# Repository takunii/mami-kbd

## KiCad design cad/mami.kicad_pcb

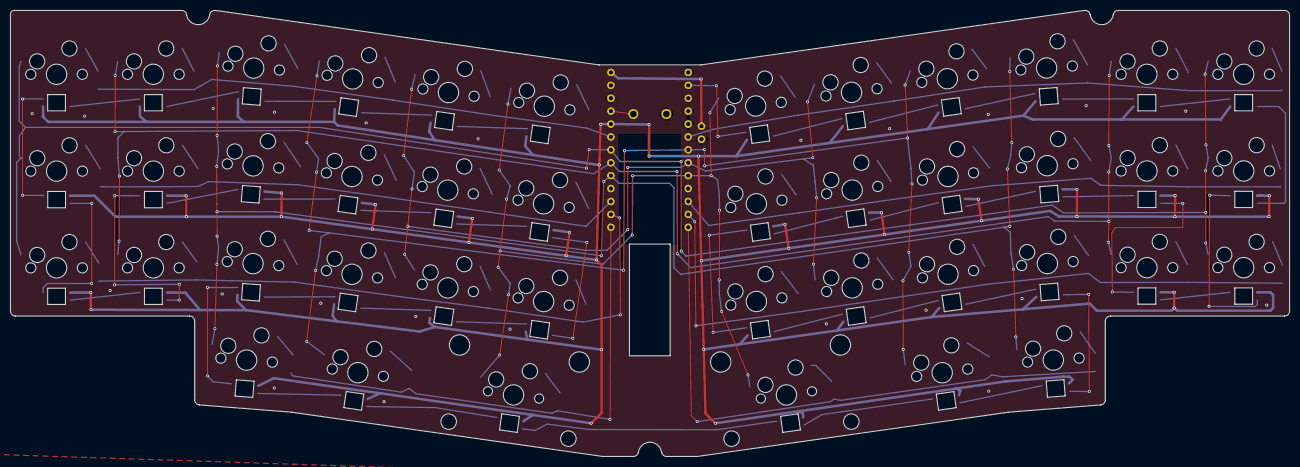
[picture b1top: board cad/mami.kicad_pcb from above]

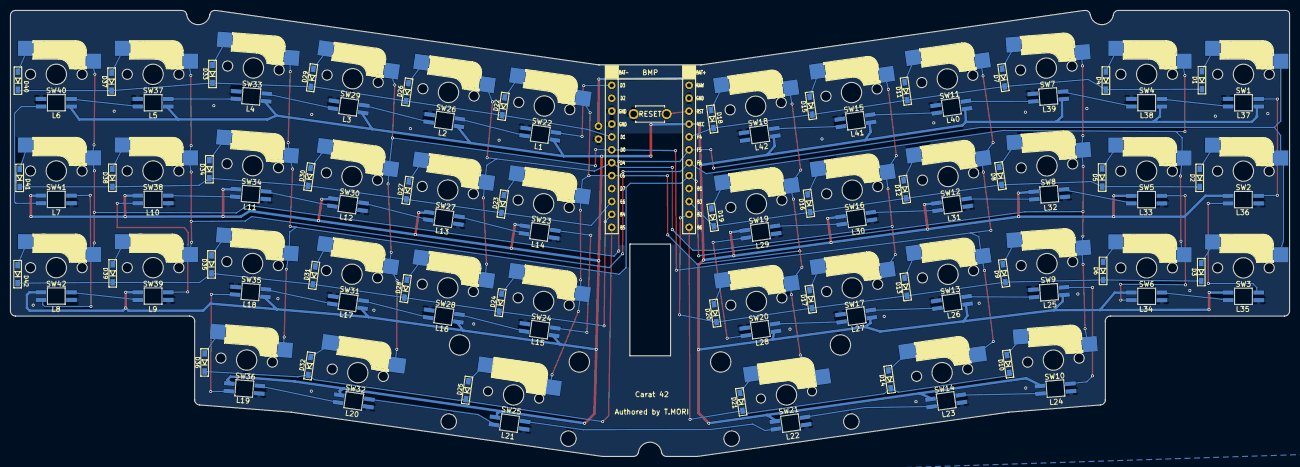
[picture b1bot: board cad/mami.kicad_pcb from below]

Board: 2 copper layers, 251.8 x 87.8 mm, 129 parts (2 on the bottom side), 102 nets.

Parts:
D1, D2, D3, D4, D5, D6, D7, D8, D9, D10, D11, D12, D13, D14, D15, D16, D17, D18, D19, D20, D21, D22, D23, D24, D25, D26, D27, D28, D29, D30, D31, D32, D33, D34, D35, D36, D37, D38, D39, D40, D41, D42: 1N4148W; Diode_SMD
J1: Conn_01x02_Pin; Battery_BMP_2pin
L1, L2, L3, L4, L5, L6, L7, L8, L9, L10, L11, L12, L13, L14, L15, L16, L17, L18, L19, L20, L21, L22, L23, L24, L25, L26, L27, L28, L29, L30, L31, L32, L33, L34, L35, L36, L37, L38, L39, L40, L41, L42: SK6812MINI-E; LED_SK6812MINI-E_BL
SW1, SW2, SW3, SW4, SW5, SW6, SW7, SW8, SW9, SW10, SW11, SW12, SW13, SW15, SW16, SW17, SW18, SW19, SW20, SW22, SW23, SW24, SW26, SW27, SW28, SW29, SW30, SW31, SW33, SW34, SW35, SW36, SW37, SW38, SW39, SW40, SW41, SW42: SW_Push; CherryMX_Hotswap_1u
SW14, SW32: SW_Push; CherryMX_Hotswap_1.25u
SW21, SW25: SW_Push; CherryMX_Hotswap_2u
SW43: ResetSW
U1: Micon_BLEMicroPro; Micon_BMP_7sKB

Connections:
BAT+: J1.2, U1.25 (BAT+)
GND: J1.1, L1.1 (VSS), L2.1 (VSS), L3.1 (VSS), L4.1 (VSS), L5.1 (VSS), L6.1 (VSS), L7.1 (VSS), L8.1 (VSS), L9.1 (VSS), L10.1 (VSS), L11.1 (VSS), L12.1 (VSS), L13.1 (VSS), L14.1 (VSS), L15.1 (VSS), L16.1 (VSS), L17.1 (VSS), L18.1 (VSS), L19.1 (VSS), L20.1 (VSS), L21.1 (VSS), L22.1 (VSS), L23.1 (VSS), L24.1 (VSS), L25.1 (VSS), L26.1 (VSS), L27.1 (VSS), L28.1 (VSS), L29.1 (VSS), L30.1 (VSS), L31.1 (VSS), L32.1 (VSS), L33.1 (VSS), L34.1 (VSS), L35.1 (VSS), L36.1 (VSS), L37.1 (VSS), L38.1 (VSS), L39.1 (VSS), L40.1 (VSS), L41.1 (VSS), L42.1 (VSS), SW43.1, U1.3 (GND), U1.4 (GND), U1.23 (GND), U1.26 (BAT-)
LED: L1.2 (DIN), U1.1 (D3/PIN1)
unnamed: D1.2 (A), SW1.2
unnamed: D2.2 (A), SW2.2
unnamed: D3.2 (A), SW3.2
unnamed: D4.2 (A), SW4.2
unnamed: D5.2 (A), SW5.2
unnamed: D6.2 (A), SW6.2
unnamed: D7.2 (A), SW7.2
unnamed: D8.2 (A), SW8.2
unnamed: D9.2 (A), SW9.2
unnamed: D10.2 (A), SW10.2
unnamed: D11.2 (A), SW11.2
unnamed: D12.2 (A), SW12.2
unnamed: D13.2 (A), SW13.2
unnamed: D14.2 (A), SW14.2
unnamed: D15.2 (A), SW15.2
unnamed: D16.2 (A), SW16.2
unnamed: D17.2 (A), SW17.2
unnamed: D18.2 (A), SW18.2
unnamed: D19.2 (A), SW19.2
unnamed: D20.2 (A), SW20.2
unnamed: D21.2 (A), SW21.2
unnamed: D22.2 (A), SW22.2
unnamed: D23.2 (A), SW23.2
unnamed: D24.2 (A), SW24.2
unnamed: D25.2 (A), SW25.2
unnamed: D26.2 (A), SW26.2
unnamed: D27.2 (A), SW27.2
unnamed: D28.2 (A), SW28.2
unnamed: D29.2 (A), SW29.2
unnamed: D30.2 (A), SW30.2
unnamed: D31.2 (A), SW31.2
unnamed: D32.2 (A), SW32.2
unnamed: D33.2 (A), SW33.2
unnamed: D34.2 (A), SW34.2
unnamed: D35.2 (A), SW35.2
unnamed: D36.2 (A), SW36.2
unnamed: D37.2 (A), SW37.2
unnamed: D38.2 (A), SW38.2
unnamed: D39.2 (A), SW39.2
unnamed: D40.2 (A), SW40.2
unnamed: D41.2 (A), SW41.2
unnamed: D42.2 (A), SW42.2
unnamed: L1.4 (DOUT), L2.2 (DIN)
unnamed: L2.4 (DOUT), L3.2 (DIN)
unnamed: L3.4 (DOUT), L4.2 (DIN)
unnamed: L4.4 (DOUT), L5.2 (DIN)
unnamed: L5.4 (DOUT), L6.2 (DIN)
unnamed: L6.4 (DOUT), L7.2 (DIN)
unnamed: L7.4 (DOUT), L8.2 (DIN)
unnamed: L8.4 (DOUT), L9.2 (DIN)
unnamed: L9.4 (DOUT), L10.2 (DIN)
unnamed: L10.4 (DOUT), L11.2 (DIN)
unnamed: L11.4 (DOUT), L12.2 (DIN)
unnamed: L12.4 (DOUT), L13.2 (DIN)
unnamed: L13.4 (DOUT), L14.2 (DIN)
unnamed: L14.4 (DOUT), L15.2 (DIN)
unnamed: L15.4 (DOUT), L16.2 (DIN)
unnamed: L16.4 (DOUT), L17.2 (DIN)
unnamed: L17.4 (DOUT), L18.2 (DIN)
unnamed: L18.4 (DOUT), L19.2 (DIN)
unnamed: L19.4 (DOUT), L20.2 (DIN)
unnamed: L20.4 (DOUT), L21.2 (DIN)
unnamed: L21.4 (DOUT), L22.2 (DIN)
unnamed: L22.4 (DOUT), L23.2 (DIN)
unnamed: L23.4 (DOUT), L24.2 (DIN)
unnamed: L24.4 (DOUT), L25.2 (DIN)
unnamed: L25.4 (DOUT), L26.2 (DIN)
unnamed: L26.4 (DOUT), L27.2 (DIN)
unnamed: L27.4 (DOUT), L28.2 (DIN)
unnamed: L28.4 (DOUT), L29.2 (DIN)
unnamed: L29.4 (DOUT), L30.2 (DIN)
unnamed: L30.4 (DOUT), L31.2 (DIN)
unnamed: L31.4 (DOUT), L32.2 (DIN)
unnamed: L32.4 (DOUT), L33.2 (DIN)
unnamed: L33.4 (DOUT), L34.2 (DIN)
unnamed: L34.4 (DOUT), L35.2 (DIN)
unnamed: L35.4 (DOUT), L36.2 (DIN)
unnamed: L36.4 (DOUT), L37.2 (DIN)
unnamed: L37.4 (DOUT), L38.2 (DIN)
unnamed: L38.4 (DOUT), L39.2 (DIN)
unnamed: L39.4 (DOUT), L40.2 (DIN)
unnamed: L40.4 (DOUT), L41.2 (DIN)
unnamed: L41.4 (DOUT), L42.2 (DIN)
VCC: L1.3 (VDD), L2.3 (VDD), L3.3 (VDD), L4.3 (VDD), L5.3 (VDD), L6.3 (VDD), L7.3 (VDD), L8.3 (VDD), L9.3 (VDD), L10.3 (VDD), L11.3 (VDD), L12.3 (VDD), L13.3 (VDD), L14.3 (VDD), L15.3 (VDD), L16.3 (VDD), L17.3 (VDD), L18.3 (VDD), L19.3 (VDD), L20.3 (VDD), L21.3 (VDD), L22.3 (VDD), L23.3 (VDD), L24.3 (VDD), L25.3 (VDD), L26.3 (VDD), L27.3 (VDD), L28.3 (VDD), L29.3 (VDD), L30.3 (VDD), L31.3 (VDD), L32.3 (VDD), L33.3 (VDD), L34.3 (VDD), L35.3 (VDD), L36.3 (VDD), L37.3 (VDD), L38.3 (VDD), L39.3 (VDD), L40.3 (VDD), L41.3 (VDD), L42.3 (VDD), U1.21 (VCC)
col0: SW1.1, SW2.1, SW3.1, SW40.1, SW41.1, SW42.1, U1.19 (F5/PIN19)
col1: SW4.1, SW5.1, SW6.1, SW37.1, SW38.1, SW39.1, U1.18 (F6/PIN18)
col2: SW7.1, SW8.1, SW9.1, SW10.1, SW33.1, SW34.1, SW35.1, SW36.1, U1.17 (F7/PIN17)
col3: SW11.1, SW12.1, SW13.1, SW14.1, SW29.1, SW30.1, SW31.1, SW32.1, U1.6 (D0/PIN6/SCL)
col4: SW15.1, SW16.1, SW17.1, SW26.1, SW27.1, SW28.1, U1.7 (D4/PIN7)
col5: SW18.1, SW19.1, SW20.1, SW21.1, SW22.1, SW23.1, SW24.1, SW25.1, U1.8 (C6/PIN8)
reset: SW43.2, U1.22 (RST)
row0: D1.1 (K), D4.1 (K), D7.1 (K), D11.1 (K), D15.1 (K), D18.1 (K), U1.20 (F4/PIN20)
row1: D2.1 (K), D5.1 (K), D8.1 (K), D12.1 (K), D16.1 (K), D19.1 (K), U1.15 (B3/PIN15)
row2: D3.1 (K), D6.1 (K), D9.1 (K), D13.1 (K), D17.1 (K), D20.1 (K), U1.14 (B2/PIN14)
row3: D10.1 (K), D14.1 (K), D21.1 (K), U1.13 (B6/PIN13)
row4: D22.1 (K), D26.1 (K), D29.1 (K), D33.1 (K), D37.1 (K), D40.1 (K), U1.5 (D1/PIN5/SDA)
row5: D23.1 (K), D27.1 (K), D30.1 (K), D34.1 (K), D38.1 (K), D41.1 (K), U1.10 (E6/PIN10)
row6: D24.1 (K), D28.1 (K), D31.1 (K), D35.1 (K), D39.1 (K), D42.1 (K), U1.11 (B4/PIN11)
row7: D25.1 (K), D32.1 (K), D36.1 (K), U1.12 (B5/PIN12)

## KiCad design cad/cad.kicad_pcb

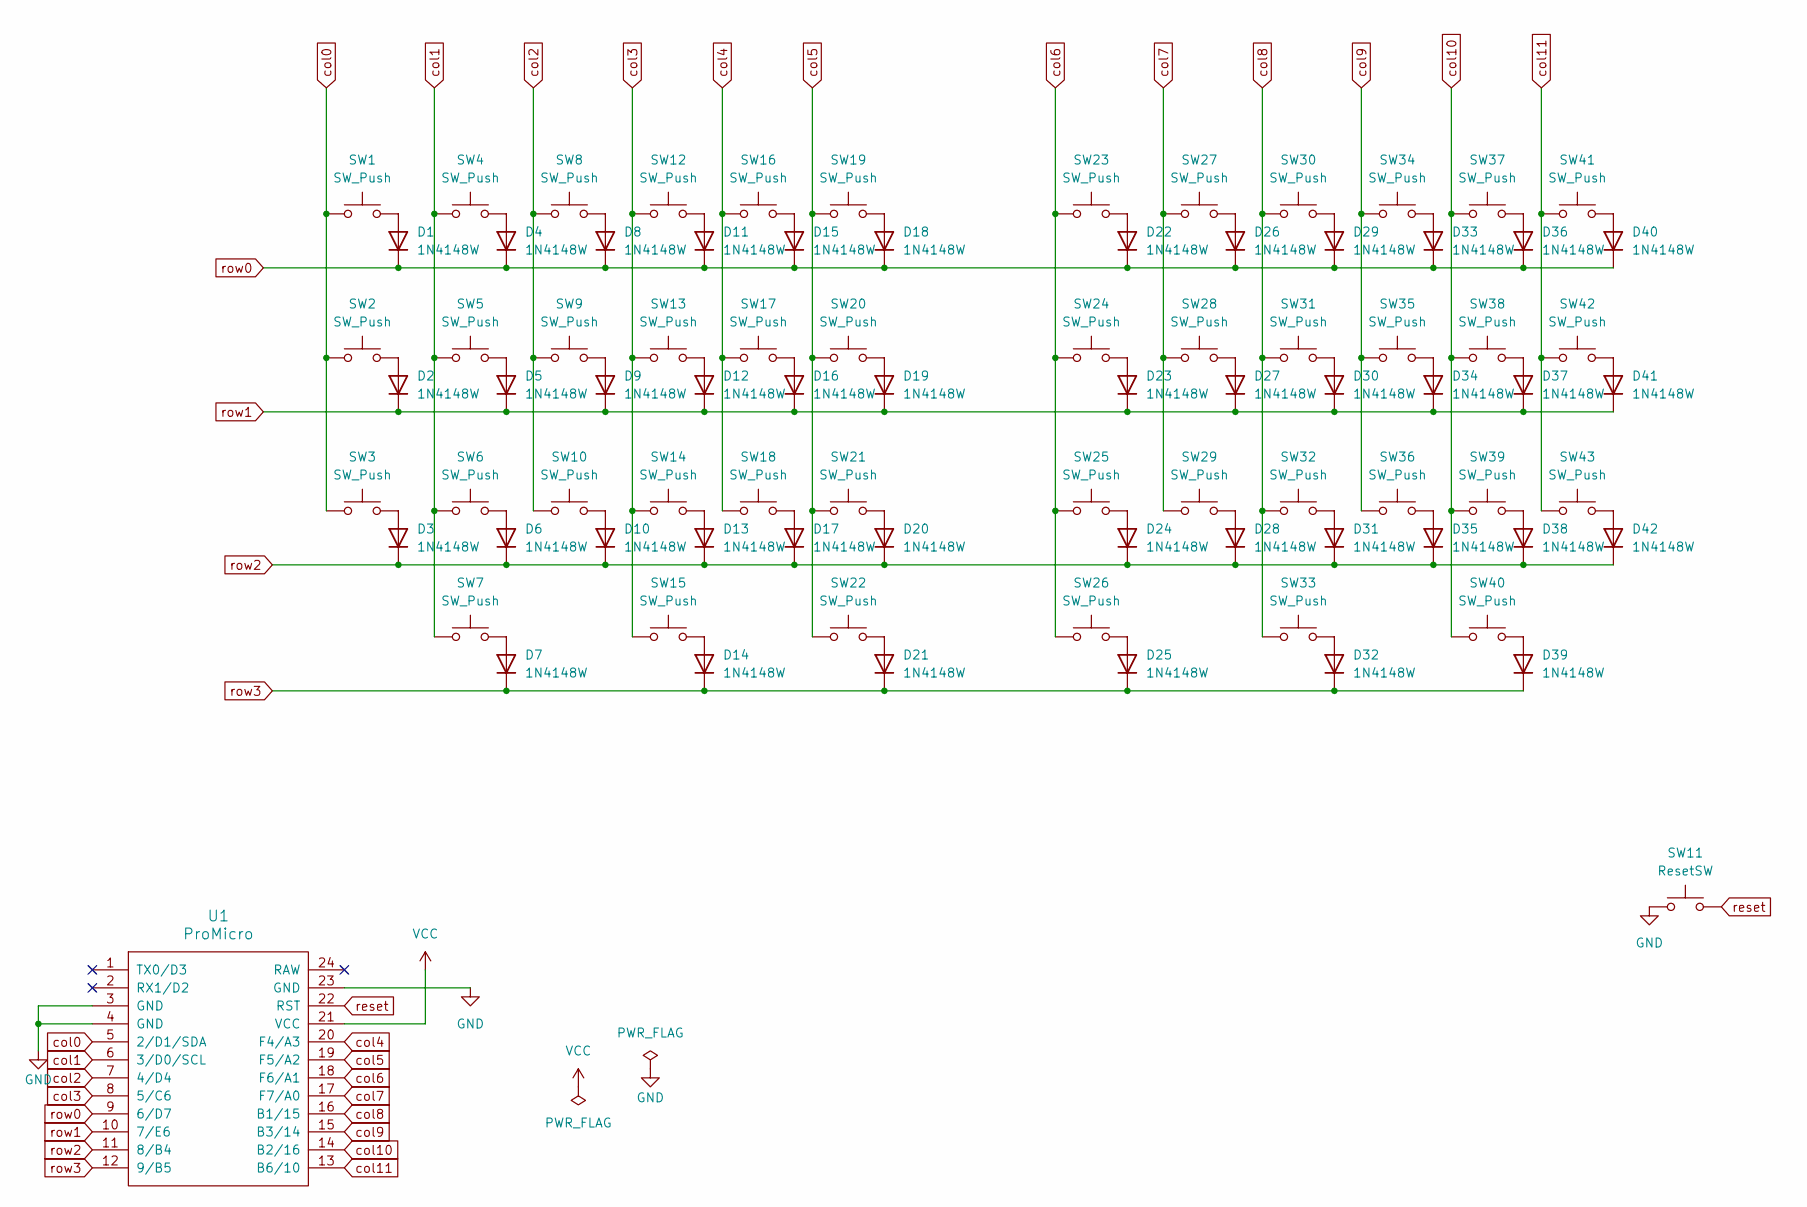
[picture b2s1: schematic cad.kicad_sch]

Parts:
D1, D2, D3, D4, D5, D6, D7, D8, D9, D10, D11, D12, D13, D14, D15, D16, D17, D18, D19, D20, D21, D22, D23, D24, D25, D26, D27, D28, D29, D30, D31, D32, D33, D34, D35, D36, D37, D38, D39, D40, D41, D42: 1N4148W; D_SOD-123
SW1, SW2, SW3, SW4, SW5, SW6, SW7, SW8, SW9, SW10, SW12, SW13, SW14, SW15, SW16, SW17, SW18, SW19, SW20, SW21, SW22, SW23, SW24, SW25, SW26, SW27, SW28, SW29, SW30, SW31, SW32, SW33, SW34, SW35, SW36, SW37, SW38, SW39, SW40, SW41, SW42, SW43: SW_Push; keyswitch_cherrymx_hotswap_1u
SW11: ResetSW
U1: ProMicro

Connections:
GND: SW11.1, U1.3 (GND), U1.4 (GND), U1.23 (GND)
unnamed: D1.2 (A), SW1.2
unnamed: D2.2 (A), SW2.2
unnamed: D3.2 (A), SW3.2
unnamed: D4.2 (A), SW4.2
unnamed: D5.2 (A), SW5.2
unnamed: D6.2 (A), SW6.2
unnamed: D7.2 (A), SW7.2
unnamed: D8.2 (A), SW8.2
unnamed: D9.2 (A), SW9.2
unnamed: D10.2 (A), SW10.2
unnamed: D11.2 (A), SW12.2
unnamed: D12.2 (A), SW13.2
unnamed: D13.2 (A), SW14.2
unnamed: D14.2 (A), SW15.2
unnamed: D15.2 (A), SW16.2
unnamed: D16.2 (A), SW17.2
unnamed: D17.2 (A), SW18.2
unnamed: D18.2 (A), SW19.2
unnamed: D19.2 (A), SW20.2
unnamed: D20.2 (A), SW21.2
unnamed: D21.2 (A), SW22.2
unnamed: D22.2 (A), SW23.2
unnamed: D23.2 (A), SW24.2
unnamed: D24.2 (A), SW25.2
unnamed: D25.2 (A), SW26.2
unnamed: D26.2 (A), SW27.2
unnamed: D27.2 (A), SW28.2
unnamed: D28.2 (A), SW29.2
unnamed: D29.2 (A), SW30.2
unnamed: D30.2 (A), SW31.2
unnamed: D31.2 (A), SW32.2
unnamed: D32.2 (A), SW33.2
unnamed: D33.2 (A), SW34.2
unnamed: D34.2 (A), SW35.2
unnamed: D35.2 (A), SW36.2
unnamed: D36.2 (A), SW37.2
unnamed: D37.2 (A), SW38.2
unnamed: D38.2 (A), SW39.2
unnamed: D39.2 (A), SW40.2
unnamed: D40.2 (A), SW41.2
unnamed: D41.2 (A), SW42.2
unnamed: D42.2 (A), SW43.2
VCC: U1.21 (VCC)
col0: SW1.1, SW2.1, SW3.1, U1.5 (2/D1/SDA)
col1: SW4.1, SW5.1, SW6.1, SW7.1, U1.6 (3/D0/SCL)
col2: SW8.1, SW9.1, SW10.1, U1.7 (4/D4)
col3: SW12.1, SW13.1, SW14.1, SW15.1, U1.8 (5/C6)
col4: SW16.1, SW17.1, SW18.1, U1.20 (F4/A3)
col5: SW19.1, SW20.1, SW21.1, SW22.1, U1.19 (F5/A2)
col6: SW23.1, SW24.1, SW25.1, SW26.1, U1.18 (F6/A1)
col7: SW27.1, SW28.1, SW29.1, U1.17 (F7/A0)
col8: SW30.1, SW31.1, SW32.1, SW33.1, U1.16 (B1/15)
col9: SW34.1, SW35.1, SW36.1, U1.15 (B3/14)
col10: SW37.1, SW38.1, SW39.1, SW40.1, U1.14 (B2/16)
col11: SW41.1, SW42.1, SW43.1, U1.13 (B6/10)
reset: SW11.2, U1.22 (RST)
row0: D1.1 (K), D4.1 (K), D8.1 (K), D11.1 (K), D15.1 (K), D18.1 (K), D22.1 (K), D26.1 (K), D29.1 (K), D33.1 (K), D36.1 (K), D40.1 (K), U1.9 (6/D7)
row1: D2.1 (K), D5.1 (K), D9.1 (K), D12.1 (K), D16.1 (K), D19.1 (K), D23.1 (K), D27.1 (K), D30.1 (K), D34.1 (K), D37.1 (K), D41.1 (K), U1.10 (7/E6)
row2: D3.1 (K), D6.1 (K), D10.1 (K), D13.1 (K), D17.1 (K), D20.1 (K), D24.1 (K), D28.1 (K), D31.1 (K), D35.1 (K), D38.1 (K), D42.1 (K), U1.11 (8/B4)
row3: D7.1 (K), D14.1 (K), D21.1 (K), D25.1 (K), D32.1 (K), D39.1 (K), U1.12 (9/B5)

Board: 2 copper layers, 86 parts (0 on the bottom side), 60 nets, no tracks yet.

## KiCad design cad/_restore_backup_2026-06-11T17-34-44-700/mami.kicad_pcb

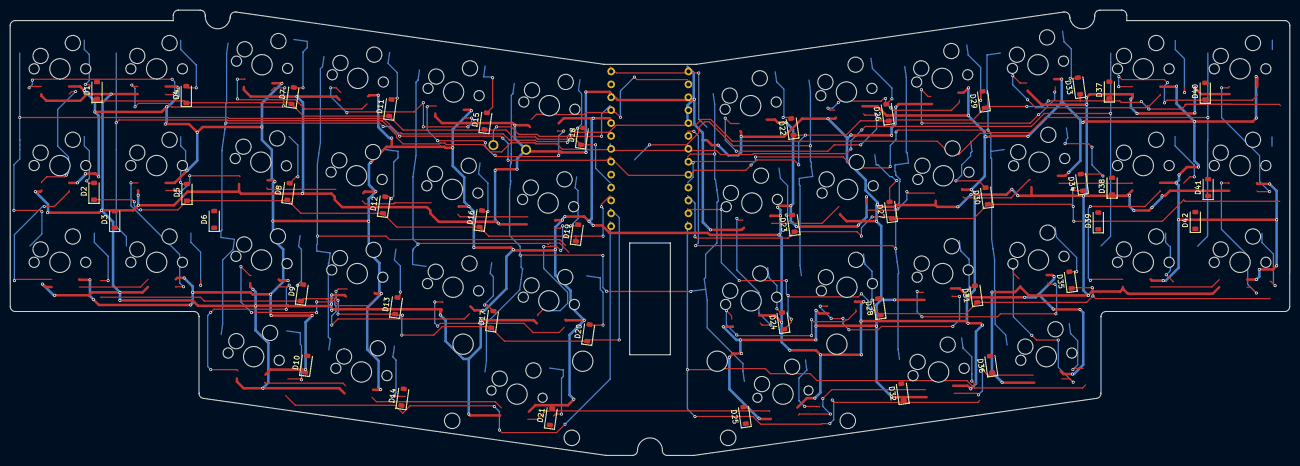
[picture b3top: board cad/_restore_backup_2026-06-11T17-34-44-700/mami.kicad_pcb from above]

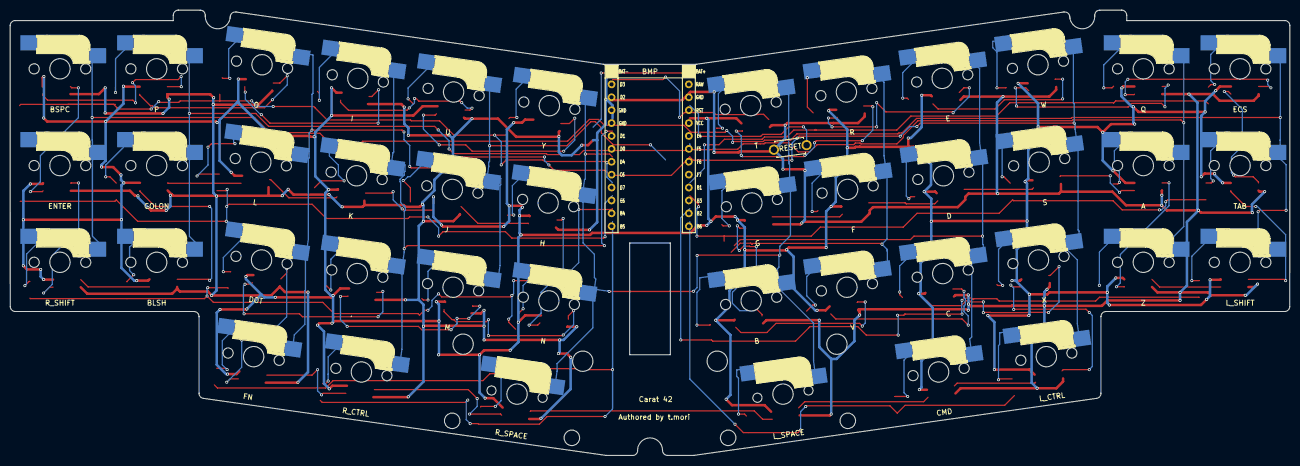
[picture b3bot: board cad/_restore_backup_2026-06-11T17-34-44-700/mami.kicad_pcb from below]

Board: 2 copper layers, 252.0 x 87.7 mm, 86 parts (2 on the bottom side), 58 nets.

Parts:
,: SW_Push; CherryMX_Hotswap_1u
A: SW_Push; CherryMX_Hotswap_1u
B: SW_Push; CherryMX_Hotswap_1u
BLSH: SW_Push; CherryMX_Hotswap_1u
BSPC: SW_Push; CherryMX_Hotswap_1u
C: SW_Push; CherryMX_Hotswap_1u
CMD: SW_Push; CherryMX_Hotswap_1.25u
COLON: SW_Push; CherryMX_Hotswap_1u
D: SW_Push; CherryMX_Hotswap_1u
D1, D2, D3, D4, D5, D6, D7, D8, D9, D10, D11, D12, D13, D14, D15, D16, D17, D18, D19, D20, D21, D22, D23, D24, D25, D26, D27, D28, D29, D30, D31, D32, D33, D34, D35, D36, D37, D38, D39, D40, D41, D42: 1N4148W; D_SOD-123
DOT: SW_Push; CherryMX_Hotswap_1u
E: SW_Push; CherryMX_Hotswap_1u
ECS: SW_Push; CherryMX_Hotswap_1u
ENTER: SW_Push; CherryMX_Hotswap_1u
F: SW_Push; CherryMX_Hotswap_1u
FN: SW_Push; CherryMX_Hotswap_1u
G: SW_Push; CherryMX_Hotswap_1u
H: SW_Push; CherryMX_Hotswap_1u
I: SW_Push; CherryMX_Hotswap_1u
J: SW_Push; CherryMX_Hotswap_1u
K: SW_Push; CherryMX_Hotswap_1u
L: SW_Push; CherryMX_Hotswap_1u
L_CTRL: SW_Push; CherryMX_Hotswap_1u
L_SHIFT: SW_Push; CherryMX_Hotswap_1u
L_SPACE: SW_Push; CherryMX_Hotswap_2u
M: SW_Push; CherryMX_Hotswap_1u
N: SW_Push; CherryMX_Hotswap_1u
O: SW_Push; CherryMX_Hotswap_1u
P: SW_Push; CherryMX_Hotswap_1u
Q: SW_Push; CherryMX_Hotswap_1u
R: SW_Push; CherryMX_Hotswap_1u
R_CTRL: SW_Push; CherryMX_Hotswap_1.25u
R_SHIFT: SW_Push; CherryMX_Hotswap_1u
R_SPACE: SW_Push; CherryMX_Hotswap_2u
S: SW_Push; CherryMX_Hotswap_1u
SW43: ResetSW
T: SW_Push; CherryMX_Hotswap_1u
TAB: SW_Push; CherryMX_Hotswap_1u
U: SW_Push; CherryMX_Hotswap_1u
U1: Micon_BLEMicroPro; Micon_BMP_7sKB
V: SW_Push; CherryMX_Hotswap_1u
W: SW_Push; CherryMX_Hotswap_1u
X: SW_Push; CherryMX_Hotswap_1u
Y: SW_Push; CherryMX_Hotswap_1u
Z: SW_Push; CherryMX_Hotswap_1u

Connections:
GND: SW43.1, U1.3 (GND), U1.4 (GND), U1.23 (GND), U1.26 (BAT-)
unnamed: D1.2 (A), ECS.2
unnamed: D2.2 (A), TAB.2
unnamed: D3.2 (A), L_SHIFT.2
unnamed: D4.2 (A), Q.2
unnamed: A.2, D5.2 (A)
unnamed: D6.2 (A), Z.2
unnamed: D7.2 (A), W.2
unnamed: D8.2 (A), S.2
unnamed: D9.2 (A), X.2
unnamed: D10.2 (A), L_CTRL.2
unnamed: D11.2 (A), E.2
unnamed: D.2, D12.2 (A)
unnamed: C.2, D13.2 (A)
unnamed: CMD.2, D14.2 (A)
unnamed: D15.2 (A), R.2
unnamed: D16.2 (A), F.2
unnamed: D17.2 (A), V.2
unnamed: D18.2 (A), T.2
unnamed: D19.2 (A), G.2
unnamed: B.2, D20.2 (A)
unnamed: D21.2 (A), L_SPACE.2
unnamed: D22.2 (A), Y.2
unnamed: D23.2 (A), H.2
unnamed: D24.2 (A), N.2
unnamed: D25.2 (A), R_SPACE.2
unnamed: D26.2 (A), U.2
unnamed: D27.2 (A), J.2
unnamed: D28.2 (A), M.2
unnamed: D29.2 (A), I.2
unnamed: D30.2 (A), K.2
unnamed: ,.2, D31.2 (A)
unnamed: D32.2 (A), R_CTRL.2
unnamed: D33.2 (A), O.2
unnamed: D34.2 (A), L.2
unnamed: D35.2 (A), DOT.2
unnamed: D36.2 (A), FN.2
unnamed: D37.2 (A), P.2
unnamed: COLON.2, D38.2 (A)
unnamed: BLSH.2, D39.2 (A)
unnamed: BSPC.2, D40.2 (A)
unnamed: D41.2 (A), ENTER.2
unnamed: D42.2 (A), R_SHIFT.2
col0: BSPC.1, ECS.1, ENTER.1, L_SHIFT.1, R_SHIFT.1, TAB.1, U1.20 (F4/PIN20)
col1: A.1, BLSH.1, COLON.1, P.1, Q.1, U1.19 (F5/PIN19), Z.1
col2: DOT.1, FN.1, L.1, L_CTRL.1, O.1, S.1, U1.18 (F6/PIN18), W.1, X.1
col3: ,.1, C.1, CMD.1, D.1, E.1, I.1, K.1, R_CTRL.1, U1.5 (D1/PIN5/SDA)
col4: F.1, J.1, M.1, R.1, U.1, U1.6 (D0/PIN6/SCL), V.1
col5: B.1, G.1, H.1, L_SPACE.1, N.1, R_SPACE.1, T.1, U1.7 (D4/PIN7), Y.1
reset: SW43.2, U1.22 (RST)
row0: D1.1 (K), D4.1 (K), D7.1 (K), D11.1 (K), D15.1 (K), D18.1 (K), U1.16 (B1/PIN16)
row1: D2.1 (K), D5.1 (K), D8.1 (K), D12.1 (K), D16.1 (K), D19.1 (K), U1.15 (B3/PIN15)
row2: D3.1 (K), D6.1 (K), D9.1 (K), D13.1 (K), D17.1 (K), D20.1 (K), U1.14 (B2/PIN14)
row3: D10.1 (K), D14.1 (K), D21.1 (K), U1.13 (B6/PIN13)
row4: D22.1 (K), D26.1 (K), D29.1 (K), D33.1 (K), D37.1 (K), D40.1 (K), U1.9 (D7/PIN9)
row5: D23.1 (K), D27.1 (K), D30.1 (K), D34.1 (K), D38.1 (K), D41.1 (K), U1.10 (E6/PIN10)
row6: D24.1 (K), D28.1 (K), D31.1 (K), D35.1 (K), D39.1 (K), D42.1 (K), U1.11 (B4/PIN11)
row7: D25.1 (K), D32.1 (K), D36.1 (K), U1.12 (B5/PIN12)

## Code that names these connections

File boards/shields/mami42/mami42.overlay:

/*
 * mami42 - 42キー Alice風一体型キーボード (nice!nano v2 / nRF52840)
 * ピンアサインは doc/pin-assignment-final.md を参照
 * row/col と物理キー座標のマッピングは doc/matrix-mapping.md と kle/layout.json を参照
 */

#include <dt-bindings/zmk/matrix_transform.h>
#include <physical_layouts.dtsi>

/ {
    chosen {
        zmk,kscan = &kscan0;
        zmk,physical-layout = &default_layout;
    };

    kscan0: kscan {
        compatible = "zmk,kscan-gpio-matrix";
        label = "KSCAN";
        diode-direction = "col2row";

        row-gpios
            = <&gpio0 31 (GPIO_ACTIVE_HIGH | GPIO_PULL_DOWN)>   // P0.31 - row0 (左側)
            , <&gpio1 11 (GPIO_ACTIVE_HIGH | GPIO_PULL_DOWN)>   // P1.11 - row1 (左側)
            , <&gpio0 10 (GPIO_ACTIVE_HIGH | GPIO_PULL_DOWN)>   // P0.10 - row2 (左側)
            , <&gpio0 9  (GPIO_ACTIVE_HIGH | GPIO_PULL_DOWN)>   // P0.09 - row3 (左側・親指)
            , <&gpio0 17 (GPIO_ACTIVE_HIGH | GPIO_PULL_DOWN)>   // P0.17 - row4 (右側)
            , <&gpio0 11 (GPIO_ACTIVE_HIGH | GPIO_PULL_DOWN)>   // P0.11 - row5 (右側)
            , <&gpio1 4  (GPIO_ACTIVE_HIGH | GPIO_PULL_DOWN)>   // P1.04 - row6 (右側)
            , <&gpio1 6  (GPIO_ACTIVE_HIGH | GPIO_PULL_DOWN)>   // P1.06 - row7 (右側・親指)
            ;

        col-gpios
            = <&gpio0 29 GPIO_ACTIVE_HIGH>   // P0.29 - col0
            , <&gpio0 2  GPIO_ACTIVE_HIGH>   // P0.02 - col1
            , <&gpio1 15 GPIO_ACTIVE_HIGH>   // P1.15 - col2
            , <&gpio0 20 GPIO_ACTIVE_HIGH>   // P0.20 - col3
            , <&gpio0 22 GPIO_ACTIVE_HIGH>   // P0.22 - col4
            , <&gpio0 24 GPIO_ACTIVE_HIGH>   // P0.24 - col5
            ;
    };

    default_transform: keymap_transform_0 {
        compatible = "zmk,matrix-transform";
        columns = <6>;
        rows = <8>;
        map =
            <
        RC(0,0)  /* SW1 */
        RC(1,0)  /* SW2 */
        RC(2,0)  /* SW3 */
        RC(0,1)  /* SW4 */
        RC(1,1)  /* SW5 */
        RC(2,1)  /* SW6 */
        RC(0,2)  /* SW7 */
        RC(1,2)  /* SW8 */
        RC(2,2)  /* SW9 */
        RC(3,2)  /* SW10 */
        RC(0,3)  /* SW11 */
        RC(1,3)  /* SW12 */
        RC(2,3)  /* SW13 */
        RC(3,3)  /* SW14 */
        RC(0,4)  /* SW15 */
        RC(1,4)  /* SW16 */
        RC(2,4)  /* SW17 */
        RC(0,5)  /* SW18 */
        RC(1,5)  /* SW19 */
        RC(2,5)  /* SW20 */
        RC(3,5)  /* SW21 */
        RC(4,5)  /* SW22 */
        RC(5,5)  /* SW23 */
        RC(6,5)  /* SW24 */
        RC(7,5)  /* SW25 */
        RC(4,4)  /* SW26 */
        RC(5,4)  /* SW27 */
        RC(6,4)  /* SW28 */
        RC(4,3)  /* SW29 */
        RC(5,3)  /* SW30 */
        RC(6,3)  /* SW31 */
        RC(7,3)  /* SW32 */
        RC(4,2)  /* SW33 */
        RC(5,2)  /* SW34 */
        RC(6,2)  /* SW35 */
        RC(7,2)  /* SW36 */
        RC(4,1)  /* SW37 */
        RC(5,1)  /* SW38 */
        RC(6,1)  /* SW39 */
        RC(4,0)  /* SW40 */
        RC(5,0)  /* SW41 */
        RC(6,0)  /* SW42 */
            >;
    };

    default_layout: default_layout {
        compatible = "zmk,physical-layout";
        display-name = "mami42";
        transform = <&default_transform>;
        kscan = <&kscan0>;

        keys  //                    w    h     x     y   rot    rx    ry
            =
          <&key_physical_attrs  100  100     0   100     0     0     0>  /* SW1 */
        , <&key_physical_attrs  100  100     0   200     0     0     0>  /* SW2 */
        , <&key_physical_attrs  100  100     0   300     0     0     0>  /* SW3 */
        , <&key_physical_attrs  100  100   100   100     0     0     0>  /* SW4 */
        , <&key_physical_attrs  100  100   100   200     0     0     0>  /* SW5 */
        , <&key_physical_attrs  100  100   100   300     0     0     0>  /* SW6 */
        , <&key_physical_attrs  100  100   214   100   800   200   100>  /* SW7 */
        , <&key_physical_attrs  100  100   228   200   800   200   100>  /* SW8 */
        , <&key_physical_attrs  100  100   241   300   800   200   100>  /* SW9 */
        , <&key_physical_attrs  100  100   250   400   800   200   100>  /* SW10 */
        , <&key_physical_attrs  100  100   314   100   800   200   100>  /* SW11 */
        , <&key_physical_attrs  100  100   328   200   800   200   100>  /* SW12 */
        , <&key_physical_attrs  100  100   341   300   800   200   100>  /* SW13 */
        , <&key_physical_attrs  125  100   350   400   800   200   100>  /* SW14 */
        , <&key_physical_attrs  100  100   414   100   800   200   100>  /* SW15 */
        , <&key_physical_attrs  100  100   428   200   800   200   100>  /* SW16 */
        , <&key_physical_attrs  100  100   441   300   800   200   100>  /* SW17 */
        , <&key_physical_attrs  100  100   514   100   800   200   100>  /* SW18 */
        , <&key_physical_attrs  100  100   528   200   800   200   100>  /* SW19 */
        , <&key_physical_attrs  100  100   541   300   800   200   100>  /* SW20 */
        , <&key_physical_attrs  200  100   475   400   800   200   100>  /* SW21 */
        , <&key_physical_attrs  100  100   786   100  (-800)  1200   100>  /* SW22 */
        , <&key_physical_attrs  100  100   773   200  (-800)  1200   100>  /* SW23 */
        , <&key_physical_attrs  100  100   760   300  (-800)  1200   100>  /* SW24 */
        , <&key_physical_attrs  200  100   726   400  (-800)  1200   100>  /* SW25 */
        , <&key_physical_attrs  100  100   886   100  (-800)  1200   100>  /* SW26 */
        , <&key_physical_attrs  100  100   873   200  (-800)  1200   100>  /* SW27 */
        , <&key_physical_attrs  100  100   860   300  (-800)  1200   100>  /* SW28 */
        , <&key_physical_attrs  100  100   986   100  (-800)  1200   100>  /* SW29 */
        , <&key_physical_attrs  100  100   973   200  (-800)  1200   100>  /* SW30 */
        , <&key_physical_attrs  100  100   960   300  (-800)  1200   100>  /* SW31 */
        , <&key_physical_attrs  125  100   926   400  (-800)  1200   100>  /* SW32 */
        , <&key_physical_attrs  100  100  1086   100  (-800)  1200   100>  /* SW33 */
        , <&key_physical_attrs  100  100  1073   200  (-800)  1200   100>  /* SW34 */
        , <&key_physical_attrs  100  100  1060   300  (-800)  1200   100>  /* SW35 */
        , <&key_physical_attrs  100  100  1051   400  (-800)  1200   100>  /* SW36 */
        , <&key_physical_attrs  100  100  1200   100     0     0     0>  /* SW37 */
        , <&key_physical_attrs  100  100  1200   200     0     0     0>  /* SW38 */
        , <&key_physical_attrs  100  100  1200   300     0     0     0>  /* SW39 */
        , <&key_physical_attrs  100  100  1300   100     0     0     0>  /* SW40 */
        , <&key_physical_attrs  100  100  1300   200     0     0     0>  /* SW41 */
        , <&key_physical_attrs  100  100  1300   300     0     0     0>  /* SW42 */
            ;
    };
};

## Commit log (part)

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2026-04-08 40 percent alice layout
2026-04-15 cadでswitchを配置
2026-04-15 キーキャップ変更 shift->1.25u caps->1u
2026-04-16 pcb update
2026-04-16 symmetric schema update pcb
2026-04-18 drawing edge
2026-04-18 make corner round
2026-04-19 silicon gasket hole
2026-04-29 回路図エディターをbattery有り＋LED有りに変更
2026-04-29 LEDのフットプリント更新
2026-04-30 LED向き変更
2026-05-01 ON/OFFスイッチを削除
2026-05-01 reverse diode direction
2026-05-01 pcb枠を修正
2026-05-01 自動配線
2026-05-01 routing width > 0.250mm
2026-05-03 make stabilizer hole upside down
2026-05-04 ラベリング
2026-05-04 自動配線エラーを修正
2026-05-04 署名を追加
2026-05-04 output step file
2026-06-06 ケースデータ修正
2026-06-10 配置変更途中
2026-06-11 libraryを追加
2026-06-11 frame chaning
2026-06-15 手動配線
2026-06-16 未接続0
2026-06-16 error 0 git add *
